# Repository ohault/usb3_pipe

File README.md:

```
                         __  _________  ____    ___  _______  ____
                        / / / / __/ _ )|_  /___/ _ \/  _/ _ \/ __/
                       / /_/ /\ \/ _  |/_ <___/ ___// // ___/ _/
                       \____/___/____/____/  /_/  /___/_/  /___/
                             Copyright (c) 2019-2026, EnjoyDigital
                                      Powered by LiteX
```

[> Intro
--------

USB3-PIPE provides **USB 3.2 SuperSpeed (Gen 1x1, 5Gbps) and SuperSpeedPlus (Gen 2x1, 10Gbps, and
Gen 1x2, 2x5Gbps, experimental) for FPGAs without any external USB chip**: the FPGA transceivers are directly connected to the USB3
connector, the PHY (USB3 PIPE + LTSSM) and a complete USB3 Device Core (Link/Protocol layers,
endpoints, device classes) are implemented in the fabric, in Migen/LiteX.

Other USB3 solutions for FPGAs rely on an external PHY ([TI TUSB1310A](http://www.ti.com/product/TUSB1310A))
or an external USB controller/FIFO ([FTDI FT60X](https://ftdichip.com/products/ft600q-b/), Infineon
[FX3](https://www.infineon.com/cms/en/product/universal-serial-bus/usb-peripheral-controllers-for-superspeed/ez-usb-fx3-usb-5-gbps-peripheral-controller/)).

**Status** (USB device, SFP2USB adapter, Linux xHCI host; Gen 1x2: experimental, two boards, see
[doc/gen1x2-hardware-validation.md](doc/gen1x2-hardware-validation.md)):

| | Gen 1x1 (5Gbps): Acorn CLE-215+ (Artix7 GTP) | Gen 2x1 (10Gbps): Alibaba XCKU3P (UltraScale+ GTY) | Gen 1x1 (5Gbps): Tang Mega 138K Pro (Gowin GW5AST GTR12) | Gen 1x2 (2x5Gbps, experimental): two Acorn Baseboard Minis + CLE-215+ (Artix7 GTP), SFP DAC cables |
|---|---|---|---|---|
| Enumeration | SuperSpeed (5000M) | SuperSpeedPlus (10000M), SuperSpeedPlus BOS capability | SuperSpeed (5000M) | SuperSpeedPlus at Gen 1x2 with a scripted USB host in gateware on the other board (enumeration-like control transfers); not yet with a USB host |
| Bulk IN/OUT | 446/449 MB/s (~90% of 5Gbps 8b/10b) | 426/466 MB/s (32-bit link), 744-785/~880 MB/s (64-bit link) | 372/433 MB/s (64-bit link at 62.5MHz) | Bulk loopback with the data checked by the scripted host (throughput not measured); PHY: 610 MB/s per direction (PRBS) |
| Full duplex | 376 + 400 MB/s | 325 + 430 MB/s (32-bit link), 619 + 736 MB/s (64-bit link) | 262 + 383 MB/s | PHY: 610 + 610 MB/s (PRBS, both directions) |
| Stability | 139 GB full duplex, data checked: 0 errors, no retry/Recovery | 156 GB full duplex (64-bit link), data checked: 0 errors, 0 LBAD, 0 Recovery | 20s runs, data checked: 0 errors, 0 LBAD, 0 Recovery | 400/400 scripted runs over 20 bitstream loads (Gen 1x2 and Gen 1x1); soak: 10000/10000 runs on one load (Gen 1x2 and Gen 1x1), 0 LBAD/retry |
| Suspend/Resume | Linux autosuspend (U3) and resume: 72/72 clean resumes (~0.6s) | | | |

Standard Linux drivers (usbfs, cdc_acm, uvcvideo, usb-storage). Demos: Bulk loopback/benchmark, LiteX
BIOS console (CDC-ACM), UVC camera up to 1080p60 (Bulk) or 1080p30 (Isochronous), Mass Storage RAM
disk (and DDR3 disk), composite camera + console.

[> Features
-----------
**PHY** (`usb3_pipe/`):
- Gen 1x1 (5Gbps): LFPS, training sequences, 8b/10b, scrambling, SKP, alignment, polarity.
- Gen 2x1 (10Gbps) on UltraScale+ GTY: SuperSpeedPlus Polling, 128b/132b, Gen 2 packet framing.
- Gen 1x2 (2x5Gbps, `lanes=2`, experimental): two lanes in lockstep, lanes deskew and swap
  (Configuration Lane detection), single lane fallback, packets at any symbol position.
- LTSSM: Polling, U0, Recovery, U1-U3, Hot/Warm Reset, Compliance, Loopback.
- Transceivers: Artix7 GTP, Kintex7 GTX, UltraScale+ GTY, Gowin GTR12, Lattice ECP5-5G DCU.
- 32, 64 or 128-bit Link Layer interface (`link_words`); the PIPE can run in its own clock
  domain (`pipe_cd`) for slower fabrics (Gowin GW5A, Lattice ECP5).
- Also generated as a standalone Verilog core (`usb3_pipe_gen`).

**USB3 Device Core** (`usb3_core/`):
- Link Layer: header flow control, retries, LMPs, timers, SuperSpeedPlus operation (Gen 2x1 and
  Gen 1x2).
- Protocol Layer, Control Endpoint (standard, class and vendor requests, Wishbone bridge).
- Bulk IN/OUT endpoints with bursts, Isochronous IN endpoints.
- U1/U2 Link Power Management (`with_lpm`), descriptors builder, debug traces.

**Device classes**: vendor Bulk, CDC-ACM (serial port, LiteX console), UVC (camera, Bulk or
Isochronous), MSC (mass storage on block RAM or DRAM), composite devices.

**Simulation**: Verilator Host model <-> PHYs <-> Device Core (`sim.py`, Gen 1x2 with `--lanes 2`),
Migen tests with Python host models (`pytest`).

*Acorn reference design (Gen 1x1 on Artix7 GTP, 32-bit Link Layer); the same PHY and core run at
Gen 2x1 on UltraScale+ GTY and on Gowin GTR12 with 64/128-bit Link Layer words.*

[> Hardware
-----------
| Board | Transceiver | Target | Status |
|---|---|---|---|
| [Acorn CLE-215+](https://github.com/enjoy-digital/litex-acorn-baseboard) on the LiteX Acorn Baseboard | Artix7 GTP | `bench/acorn.py` | Gen 1 validated, main development target |
| Alibaba Cloud XCKU3P | UltraScale+ GTY | `bench/alibaba_xcku3p.py` | Gen 1 and Gen 2 validated, main Gen 2 target |
| [Sipeed Tang Mega 138K Pro](https://wiki.sipeed.com/hardware/en/tang/tang-mega-138k/mega-138k-pro.html) | Gowin GW5AST GTR12 | `bench/sipeed_tang_mega_138k_pro.py` | Gen 1 validated |
| [LambdaConcept ECPIX-5](https://shop.lambdaconcept.com/home/46-ecpix-5.html) | Lattice ECP5-5G DCU | `bench/lambdaconcept_ecpix5.py` | Gen 1 validated: IN 434MB/s, OUT 449MB/s (on-board USB-C, open source toolchain) |
| Gowin GW5AT-15 | Gowin GTR12 | SerDes in `usb3_pipe/gw5`, no target | Gen 1 validated: IN ~400MB/s (direct USB-C) |
| [KC705](https://www.xilinx.com/products/boards-and-kits/ek-k7-kc705-g.html) | Kintex7 GTX | `bench/kc705.py` | Build-tested, hardware validation in progress |
| Two [LiteX Acorn Baseboard Minis](https://github.com/enjoy-digital/litex-acorn-baseboard) + Acorn CLE-215+, two SFP DAC cables | Artix7 GTP (both SFP cages) | `bench/acorn.py --lanes 2` | Gen 1x2 (experimental) between the two boards: PHY and Device Core with a scripted host, not yet with a USB host |

The boards without a USB connector use a [SFP2USB](http://xillybus.com/sfp2usb-module) adapter in
a SFP cage, or the [PCIsh-to-USB3.0](doc/breakout_board.pdf) breakout board
([gerbers](doc/breakout_board_gerbers.zip)). The Gowin and ECP5 targets need the GTR12 and 40-bit
`SerDesECP5` support of [LiteICLink](https://github.com/enjoy-digital/liteiclink).

Any board with a supported transceiver routed to a SFP, PCIe or USB-C connector can be used with a
target file: the example designs are shared (`usb3_core/examples.py`). Gen 2 needs 10Gbps capable
transceivers (validated on UltraScale+ GTY).

[> Getting started
------------------
Prerequisites: Python 3.9 or newer, LiteX installed with `litex_setup.py --config=standard`
([installation guide](https://github.com/enjoy-digital/litex/wiki/Installation)), Verilator for
the simulations, Vivado or the Gowin IDE for the boards.

```sh
$ git clone https://github.com/enjoy-digital/usb3_pipe && cd usb3_pipe
$ pip3 install -e .
```

Host tools and user access to the device:

```sh
$ pip3 install pyusb libusb1
$ sudo cp bench/99-usb3-pipe.rules /etc/udev/rules.d/ && sudo udevadm control --reload
```

Simulation (Verilator): Host model <-> SerDes models <-> Device PHY + USB3 Device Core.

```sh
$ ./sim.py                         # Gen 1: link training, enumeration, Bulk transfers.
$ ./sim.py --gen2 --link-words 2   # Gen 2x1 (10Gbps) with the 64-bit Link Layer.
$ ./sim.py --lanes 2 --lanes-core  # Gen 1x2 (2x5Gbps, experimental): SuperSpeedPlus on two lanes.
$ ./sim.py --help                  # Host model scenarios, pipe_cd, two lanes, VCD trace.
```

Hardware: build and load a target, check the enumeration, run a host script. The scripts given a
`--csr-csv` connect to a `litex_server` on the board bridge; `usb3_bulk.py` only needs libusb.

```sh
# Acorn CLE-215+ (Artix7 GTP, Gen 1): Bulk loopback example.
$ ./bench/acorn.py --build --load --with-jtagbone
$ lsusb -t                                           # 5000M, driver usbfs.
$ ./bench/usb3_bulk.py loopback --size 1024 --count 1000

# Alibaba XCKU3P (UltraScale+ GTY, Gen 2): bench example, 64-bit Link Layer.
$ ./bench/alibaba_xcku3p.py --build --load --example bench --gen2-capable --link-words 2
$ lsusb -t                                           # 10000M on a USB 3.2 Gen 2 root hub port, 5000M on a Gen 1 port.
$ litex_server --jtag --jtag-config <openocd config> # JTAGBone (manual: Getting started), in another terminal.
$ ./bench/usb3_bench.py both --transfer-size 65536 --csr-csv build/alibaba_xcku3p/csr.csv

# Sipeed Tang Mega 138K Pro (Gowin GW5AST GTR12, Gen 1): bench example, 64-bit Link Layer, 62.5MHz.
$ ./bench/sipeed_tang_mega_138k_pro.py --build --example bench
$ openFPGALoader -c ft2232 build/sipeed_tang_mega_138k_pro/gateware/impl/pnr/project.fs
$ litex_server --uart --uart-port /dev/ttyUSBx      # UARTBone (default bridge).
$ ./bench/usb3_bench.py both --transfer-size 65536 --csr-csv build/sipeed_tang_mega_138k_pro/csr.csv
```

`usb3_bench.py` uses 1MB transfers by default: with them the host limits the Gen 2 Bulk IN rate
(~330MB/s), `--transfer-size 65536` measures the device.

[> Demos
--------
Build with `./bench/acorn.py --build --load --example <name>`:

| Example | Device | Host side |
|---|---|---|
| `loopback` | Vendor Bulk OUT -> Bulk IN | `bench/usb3_bulk.py loopback` |
| `wishbone` | `loopback` + EP0 Wishbone bridge (vendor requests) | `litex_server --usb --usb-vid 0x1d50 --usb-pid 0x605a` |
| `bench` | Vendor Bulk counters source/checker | `bench/usb3_bench.py in\|out\|both` |
| `cdc_uartbone` | CDC-ACM serial port (UARTBone) | `litex_server --uart --uart-port /dev/ttyACM0` |
| `console` (`--cpu-type vexriscv`) | CDC-ACM LiteX BIOS console | `litex_term /dev/ttyACM0` |
| `uvc` | UVC camera, YUY2 test pattern (480p60/720p60/1080p30/1080p60) | `ffplay -f v4l2 -video_size 1920x1080 /dev/video0`, VLC |
| `uvc_iso` | UVC camera, Isochronous streaming (480p60/720p30/720p60/1080p30) | `ffplay -f v4l2 -video_size 1280x720 /dev/video0`, VLC |
| `msc` | Mass Storage 512KB FAT RAM disk | `/dev/sdX`, mount |
| `msc_dram` | Mass Storage 512MB DDR3 disk (not yet validated on hardware) | `mkfs.vfat /dev/sdX`, mount |
| `composite` (`--cpu-type vexriscv`) | UVC camera + CDC-ACM console | both at the same time |

The other targets build the same examples, except `msc_dram` (no DRAM controller). Common options:
`--link-words 1|2|4`, `--max-burst`, `--with-lpm`, `--lean`, `--with-analyzer`.

[> Standalone core generation
-----------------------------
The PHY, optionally with the Device Core (Bulk IN/OUT AXI-Stream endpoints), can be generated as a
standalone Verilog core (Gen 1x1, Artix7 GTP/Kintex7 GTX/UltraScale+ GTY) from a YAML description,
for designs not built with LiteX:
```sh
$ usb3_pipe_gen examples/a7_usb_device.yml --output-dir build/usb3_device
```
The YAML keys, interfaces and outputs are described in the Integration chapter of the manual.

[> Documentation
----------------
The **USB 3.2 PHY & Core manual** is the reference of the project, from the primers to the integration,
the examples, the debugging and the registers:

- Read it: [PDF](https://github.com/enjoy-digital/usb3_pipe/releases/download/manual-nightly/usb3_pipe_manual.pdf) or
  [HTML](https://github.com/enjoy-digital/usb3_pipe/releases/download/manual-nightly/usb3_pipe_manual.html) (rebuilt nightly).
- Sources and local build: [doc/manual](doc/manual/README.md).
- Gen 2 and multi-lane roadmap: [doc/notes/gen2-x2-roadmap.md](doc/notes/gen2-x2-roadmap.md).
- Gen 1x2 hardware validation (procedure and results between two boards):
  [doc/gen1x2-hardware-validation.md](doc/gen1x2-hardware-validation.md).

[> Tests
--------
```sh
$ pytest test                                 # Default suite: Migen tests + short Verilator simulations (marker sim).
$ pytest test -n auto -m "not slow and not sim" # Without Verilator, in parallel (pytest-xdist).
$ pytest test -m slow                         # Long Verilator simulations, run nightly by the CI.
```
The CI runs the Migen tests and the Verilator simulations on every push, the long simulations
nightly.

[> Contributing
---------------
See [CONTRIBUTING.md](CONTRIBUTING.md): tests and markers, LiteX coding style, commit/pull request
rules, hardware safety rules. Pull requests go against the default branch, one topic per pull
request.

[> License
----------
USB3-PIPE is released under the very permissive two-clause BSD license. Under the terms of this
license, you are authorized to use USB3-PIPE for closed-source proprietary designs.
Even though we do not require you to do so, those things are awesome, so please do them if possible:
 - tell us that you are using USB3-PIPE
 - cite USB3-PIPE in publications related to research it has helped
 - send us feedback and suggestions for improvements
 - send us bug reports when something goes wrong
 - send us the modifications and improvements you have done to USB3-PIPE.

[> Support and consulting
-------------------------
We love open-source hardware and like sharing our designs with others.

USB3-PIPE is developed and maintained by EnjoyDigital.

If you would like to know more about USB3-PIPE or if you are already a happy user and would like to
extend it for your needs, EnjoyDigital can provide standard commercial support as well as consulting
services.

So feel free to contact us, we'd love to work with you!

[> Contact
----------
E-mail: florent [AT] enjoy-digital.fr

[> Credits
----------
- [bunnie](https://www.bunniestudios.com/) for the [PCIsh-to-USB3.0](doc/breakout_board.pdf) breakout board
  used for the initial development.
- [Antmicro](https://antmicro.com/) and [Google](https://opensource.google/) for sponsoring the initial
  development of the project.
- The [Daisho](https://github.com/greatscottgadgets/daisho) project for its USB3 core, used initially with
  USB3-PIPE ([customized](https://github.com/enjoy-digital/daisho)) before the native USB3 Device Core.

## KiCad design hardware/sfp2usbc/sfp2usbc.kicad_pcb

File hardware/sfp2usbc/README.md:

# Dual SFP to USB-C breakout (USB 3.2 Gen 1x2)

Passive breakout for USB3-PIPE Gen 1x2 (2x5Gbps) hardware tests
([issue #140](https://github.com/enjoy-digital/usb3_pipe/issues/140),
[gen2-x2-roadmap.md](../../doc/gen2-x2-roadmap.md#gen-1x2-hardware-milestones), M1): two SFP cages
on one side, a USB Type-C receptacle on the other. The LiteX Acorn Baseboard Mini SFP-0/SFP-1
(Lane 0/Lane 1 of `bench/acorn.py --lanes 2`) are connected to the cages with two passive SFP DAC
cables, the USB-C to a USB 3.2 Gen 1x2/Gen 2x2 host with a full-featured USB-C cable.

```
 Acorn Baseboard Mini                       Breakout                                  Host
 FPGA GTP Lane 1 TX ── SFP-1 ══ DAC ══ J2 RD ── C3/C4 (AC) ──┬── J3 TX2 (B2/B3) ══ USB-C ══ RX
 FPGA GTP Lane 1 RX ── SFP-1 ══ DAC ══ J2 TD ────────────────┼── J3 RX2 (A11/A10)          TX (AC at host)
 FPGA GTP Lane 0 TX ── SFP-0 ══ DAC ══ J1 RD ── C1/C2 (AC) ──┼── J3 TX1 (A3/A2)
 FPGA GTP Lane 0 RX ── SFP-0 ══ DAC ══ J1 TD ────────────────┴── J3 RX1 (B11/B10)
                                                       U1/U2 ESD, R1/R2 Rd on CC1/CC2
```

J2 (Lane 1, Acorn SFP-1) is the top cage, J1 (Lane 0, Acorn SFP-0) the bottom cage (as the USB-C
TX2/RX2 and TX1/RX1 pins: no crossings).

## Files

| File | Role |
|---|---|
| [netlist.py](netlist.py) | Design intent: components, pins, nets (single source of truth). |
| [gen_schematic.py](gen_schematic.py) | Generates `sfp2usbc.kicad_sch` from netlist.py (KiCad library symbols, net labels, footprints). |
| [gen_board.py](gen_board.py) | Generates `sfp2usbc.kicad_pcb` (4 layers, outline, footprints/nets, placement, routing), `sfp2usbc.kicad_pro` (net classes) and `sfp2usbc.kicad_dru` (custom rules). |
| [route_board.py](route_board.py) | Routing (called by gen_board.py): planned pair routes, vias, GND planes/pours, stitching. |
| [check_netlist.py](check_netlist.py) | Checks a KiCad netlist export against netlist.py. |
| [backplane-brief.md](backplane-brief.md) | Review and fab outputs with Backplane (or in KiCad). |
| [sfp2usbc-schematic.pdf](sfp2usbc-schematic.pdf), [sfp2usbc-top.png](sfp2usbc-top.png), [sfp2usbc-bottom.png](sfp2usbc-bottom.png) | Previews (schematic, routing on F.Cu/B.Cu without the GND pours). |
| [3d/gen_models.py](3d/gen_models.py) | 3D models (VRML) of the parts missing from the KiCad 3D library: SFP cage + connector (TE 2227302), USB-C receptacle (Amphenol 12401610E4#2A, no model in KiCad 7). Referenced by the board as `${KIPRJMOD}/3d/*.wrl`. |
| [sfp2usbc-3d-sfp-side.png](sfp2usbc-3d-sfp-side.png), [sfp2usbc-3d-usb-side.png](sfp2usbc-3d-usb-side.png) | 3D views of the assembled board (KiCad 3D viewer, raytracing). |

```sh
# KiCad 7+ (kicad-cli, pcbnew Python module).
$ ./gen_schematic.py
$ kicad-cli sch export netlist --format kicadsexpr -o sfp2usbc.net sfp2usbc.kicad_sch
$ ./check_netlist.py sfp2usbc.net        # 0 errors.
$ ./gen_board.py --drc drc.rpt           # Routed board + DRC report (clean).
```

`gen_board.py` overwrites the board: once it is edited in KiCad, change the schematic (regenerated
from netlist.py) and use KiCad's "Update PCB from Schematic" (footprints linked to the schematic
symbols) instead of regenerating the board. Tests: `test/test_sfp2usbc_netlist.py` (netlist, KiCad
schematic/board round trips, DRC, pairs skew).

## Design decisions

- **AC coupling on this board, FPGA TX paths only.** The Acorn Baseboard Mini SFP lanes are DC
  coupled to the GTPs (schematic rev 0.2: "SFP: AC coupling on modules by standard") and passive DAC
  cables are DC: the USB3 transmitter AC coupling (75-265nF, 100nF as the SFP2USB adapter) is on the
  breakout, between the SFP RD pins (FPGA TX, after the DAC crossover) and the USB-C TX pins. The
  host AC couples its own TX: no capacitor on the RX paths.
- **Lane mapping.** J1 (bottom cage, to Acorn SFP-0, USB3PHY Lane 0) on TX1/RX1, J2 (top cage, to
  Acorn SFP-1, Lane 1) on TX2/RX2. With the plug in the CC1 orientation, the Configuration Lane
  (Lane 0) is TX1/RX1: lanes match. With the plug flipped, the lanes are swapped: handled in
  gateware (below).
- **Plug orientation in gateware, not with a CC controller.** Passive DAC cables do not carry the SFP
  low-speed pins (I2C, MOD_ABS...) to the other end: a CC controller on the breakout cannot be read by
  the FPGA. The host sends the SuperSpeedPlus Polling LFPS on its Configuration Lane only: the
  USB3PHY can detect the lane receiving them and swap the lanes (to do, roadmap M1). The R1/R2 pads
  give the orientation on the bench (the CC with ~0.4V-2V on its Rd is the active one).
- **UFP (device) Rd on CC1/CC2** (5.1k 1%): the host sources VBUS and enables SuperSpeed. No VCONN,
  no USB PD. VBUS is not used: the 4 VBUS pins joined, to a bottom test pad (TP1).
- **No USB 2.0** (as the SFP2USB adapter, works with Linux xHCI hosts): D+/D- and SBU1/SBU2 not
  connected.
- **P/N swaps.** USB3 receivers invert their RX polarity (host and USB3PHY, per lane, USB 3.2
  6.4.2/6.13.7), the Acorn baseboard already inverts some pairs. The routing has no crossings with
  two swaps: Lane 1 SSRX on the SFP side (J2 TD- = L1_SSRX_P: FPGA RX Lane 1 inverted) and Lane 0
  SSTX on the USB-C side (A3 TX1- = L0_SSTX_P: host RX Lane 0 inverted).
- **SFP low-speed/power pins not connected** (VccT/VccR, TX_DISABLE, MOD_DEF0-2, RS0/RS1, LOS,
  TX_FAULT): nothing to power or read in a passive DAC plug for this use.
- **ESD**: low capacitance 4-line arrays (U1/U2, TI TPD4E05U06, 0.5pF) on the USB-C side of the
  AC capacitors, close to J3. Flow-through routing: each line runs over its pad pair (1/10, 2/9,
  4/7, 5/6), the NC pads (not internally connected) are on the line's net, SSRX on the top rows,
  SSTX on the bottom rows (lines assigned in the routing order), GND vias on both sides.
- **Shield**: 1M || 100nF to GND (R3/C5, as the SFP2USB adapter). Cages to GND.

## Pin mapping

SFP host connector (SFF-8431 pinout): 1/10/11/14/17/20 VeeT/VeeR (GND), 12 RD-, 13 RD+, 18 TD+,
19 TD-, 2-9/15/16 low-speed/power (not connected). Through the DAC cable, the Acorn TD (FPGA TX)
arrives on the breakout RD pins and the breakout TD pins go to the Acorn RD (FPGA RX).

| Net | SFP | AC cap | USB-C | ESD |
|---|---|---|---|---|
| L0_SFP_RD_P / L0_SSTX_P | J1.13 (RD+) | C1 | A3 (TX1-, swapped) | U1.4/7 |
| L0_SFP_RD_N / L0_SSTX_N | J1.12 (RD-) | C2 | A2 (TX1+, swapped) | U1.5/6 |
| L0_SSRX_P | J1.18 (TD+) | - | B11 (RX1+) | U1.2/9 |
| L0_SSRX_N | J1.19 (TD-) | - | B10 (RX1-) | U1.1/10 |
| L1_SFP_RD_P / L1_SSTX_P | J2.13 (RD+) | C3 | B2 (TX2+) | U2.4/7 |
| L1_SFP_RD_N / L1_SSTX_N | J2.12 (RD-) | C4 | B3 (TX2-) | U2.5/6 |
| L1_SSRX_P | J2.19 (TD-, swapped) | - | A11 (RX2+) | U2.1/10 |
| L1_SSRX_N | J2.18 (TD+, swapped) | - | A10 (RX2-) | U2.2/9 |
| CC1 / CC2 | | | A5 / B5 | R1 / R2 5.1k to GND |
| VBUS | | | A4/A9/B4/B9 | TP1 (bottom) |
| SHIELD | | | Shell | R3 1M, C5 100nF to GND |
| GND | 1/10/11/14/17/20, cages | | A1/A12/B1/B12 | U1/U2.3/8 |

## Bill of materials

| Ref | Part | KiCad footprint | Notes |
|---|---|---|---|
| J1, J2 | SFP 20-pin connector + 1x1 press-fit cage (TE drawing 2227302) | `Connector:Connector_SFP_and_Cage` | Order the connector and the cage per the TE drawing; PCB edge 43mm from the footprint origin. |
| J3 | Amphenol 12401610E4#2A (USB-C, 24 pins, USB 3.2, R/A SMT) | `Connector_USB:USB_C_Receptacle_Amphenol_12401610E4-2A` | All 4 SuperSpeed pairs (the 16-pin USB 2.0 receptacles, ex GCT USB4085, do not fit). Alternative: Molex 105450-0101. |
| C1-C4 | 100nF X7R 0402, 16V | `Capacitor_SMD:C_0402_1005Metric` | USB3 75-265nF. |
| U1, U2 | TI TPD4E05U06DQAR | `Package_SON:USON-10_2.5x1.0mm_P0.5mm` | 0.5pF, flow-through. |
| R1, R2 | 5.1k 1% 0402 | `Resistor_SMD:R_0402_1005Metric` | Rd (UFP). |
| R3, C5 | 1M 0402, 100nF 0402 | 0402 | Shield. |
| TP1 | VBUS test pad (bottom side) | `TestPoint:TestPoint_Pad_D1.0mm` | |
| H1-H4 | M3 mounting holes | `MountingHole:MountingHole_3.2mm_M3` | |

Check the datasheets, availability and footprints (pad sizes, J3 front/board edge position) before
ordering.

## PCB

Generated (gen_board.py + route_board.py), DRC clean (KiCad 7: 0 violations, 0 unconnected).

- **Stackup**: 4 layers, 1.6mm: F.Cu signals, In1.Cu/In2.Cu solid GND planes, B.Cu signals (USB-C B
  row pairs, CC2, VBUS, shield ring), GND pours on F.Cu/B.Cu, GND stitching vias (3mm grid where
  free). Set the fab's controlled impedance stackup.
- **Impedance**: 90 ohm differential (USB 3.2; SFP is 100 ohm: negligible on a few cm), net class
  `HS_90R` (all `L*` nets) with 0.30mm width/0.20mm gap: estimate for a ~0.21mm prepreg, to replace
  with the fab's stackup/impedance calculator values (then regenerate: PAIR_PITCH/HS_WIDTH in
  route_board.py). Custom rule: 0.25mm between the HS tracks and the other nets outside the fine
  pitch footprints.
- **Placement**: 78 x 50mm, cages on the left edge (TE 2227302 PCB edge), J3 on the right edge, AC
  caps in line with the SFP RD pads (staggered), ESD arrays (flow-through) between the caps and J3,
  Rd/shield parts next to J3, 4 M3 holes on the right half (the cages take the left half).
- **Routing** (per lane, nested L-shaped routes with 45 degrees corners, no crossings):
  - USB-C A row pairs (L1 SSRX, L0 SSTX) on F.Cu end to end, no vias.
  - USB-C B row pairs (L1 SSTX, L0 SSRX): F.Cu from the SFP to the ESD, then 0.35/0.2mm vias
    (staggered 0.6mm, GND stitching via next to them), B.Cu, and 0.35/0.2mm vias in front of the B
    row (two staggered columns under the connector body: tented), F.Cu stubs to the B pads. A row
    GND/VBUS pins joined to their B row pins across the rows.
  - Lengths 34-36mm per line (lanes within ~2mm, deskewed by the USB3PHY), intra-pair skew <=
    0.043mm: the B row pairs P line (outer via column) is matched with 3 bumps on the N line.
- **Fab**: 0.35mm vias with 0.2mm drills (0.075mm annular ring), 0.15mm clearances, 0.25mm hole
  clearance, 0.25mm copper to edge (J3 footprint: 0.298mm between a NPTH and a shell pad): check
  them against the fab capabilities.
- **To review in KiCad**: impedance values, return paths (GND planes are solid under all the pairs),
  the J3/SFP footprints vs datasheets, the vias under the J3 body (tented), silkscreen.
- **Outputs**: Gerbers, drill, IPC netlist, BOM, placement (CPL), fab stackup/impedance notes.
- **3D**: KiCad 3D viewer (View > 3D Viewer, Preferences > Raytracing) with the KiCad 3D library
  (0402, USON-10) and the `3d/` models (approximate shapes: use the manufacturers' STEP files for
  enclosure work). The previews are KiCad 7 3D viewer raytraced views; KiCad 8+:
  `kicad-cli pcb render --quality high` for the same renders from the command line.

## Bring-up

1. Continuity/impedance: no short between pairs, Rd 5.1k on CC1/CC2, AC caps in series on the TX paths.
   DAC cables: Acorn SFP-0 to J1 (bottom cage), SFP-1 to J2 (top cage).
2. Acorn `bench/acorn.py --lanes 2 --role device` on both SFPs through the breakout and DAC cables
   (<= 1m, passive), a full-featured USB-C cable (all SuperSpeed pairs: "USB 10Gbps/20Gbps" rated)
   to a USB 3.2 Gen 2x2 host (Gen 1x2 support: ex ASMedia ASM3242).
3. `./bench/usb3_lanes.py status`: SuperSpeedPlus Polling with Gen 1x2 negotiated (x2) and link
   training, both plug orientations (flipped: lanes swapped, until the gateware lane swap is done).
   The `--lanes 2` bitstream has no Link Layer: the host does not enumerate it (the link leaves U0).
   Linux `/sys/bus/usb/devices/*/rx_lanes`/`tx_lanes` once the Gen 1x2 Link Layer is done.
4. Single lane (Gen 1x1) hosts: needs the single lane fallback in the USB3PHY (roadmap).

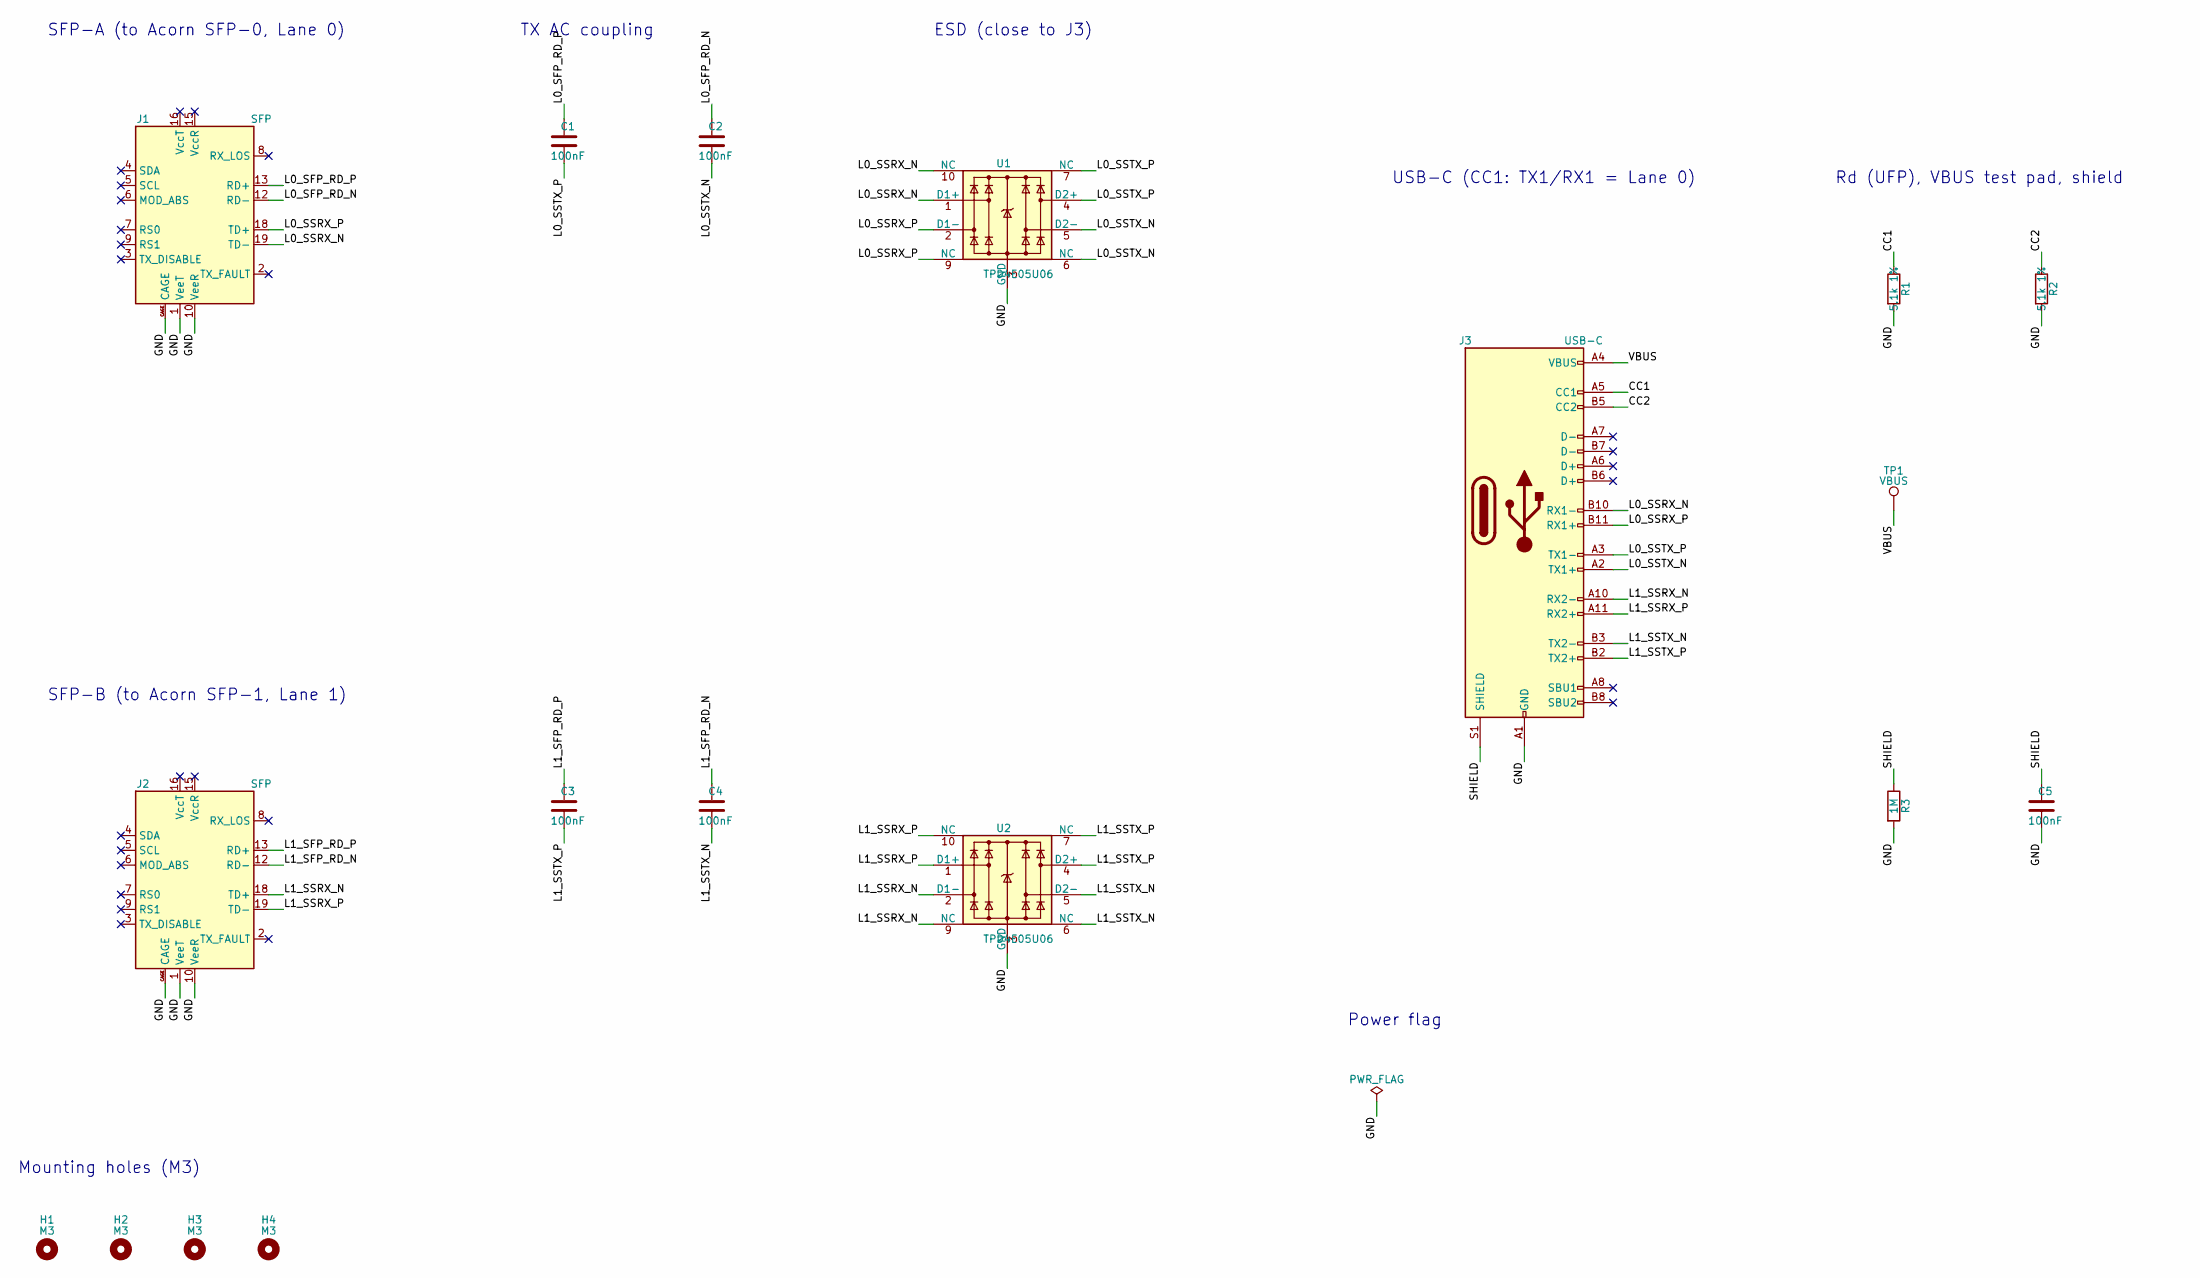
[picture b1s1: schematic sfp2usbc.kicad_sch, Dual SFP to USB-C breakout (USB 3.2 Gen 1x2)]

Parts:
C1, C2, C3, C4, C5: 100nF; C_0402_1005Metric
H1, H2, H3, H4: M3; MountingHole_3.2mm_M3
J1, J2: SFP; Connector_SFP_and_Cage
J3: USB-C; USB_C_Receptacle_Amphenol_12401610E4-2A
R1, R2: 5.1k 1%; R_0402_1005Metric
R3: 1M; R_0402_1005Metric
TP1: VBUS; TestPoint_Pad_D1.0mm
U1, U2: TPD4E05U06; USON-10_2.5x1.0mm_P0.5mm

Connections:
/CC1: J3.A5 (CC1), R1.1
/CC2: J3.B5 (CC2), R2.1
/GND: C5.2, J1.1 (VeeT), J1.10 (VeeR), J1.11 (VeeR), J1.14 (VeeR), J1.17 (VeeT), J1.20 (VeeT), J1.CAGE, J2.1 (VeeT), J2.10 (VeeR), J2.11 (VeeR), J2.14 (VeeR), J2.17 (VeeT), J2.20 (VeeT), J2.CAGE, J3.A1 (GND), J3.A12 (GND), J3.B1 (GND), J3.B12 (GND), R1.2, R2.2, R3.2, U1.3 (GND), U1.8 (GND), U2.3 (GND), U2.8 (GND)
/L0_SFP_RD_N: C2.1, J1.12 (RD-)
/L0_SFP_RD_P: C1.1, J1.13 (RD+)
/L0_SSRX_N: J1.19 (TD-), J3.B10 (RX1-), U1.1 (D1+), U1.10 (NC)
/L0_SSRX_P: J1.18 (TD+), J3.B11 (RX1+), U1.2 (D1-), U1.9 (NC)
/L0_SSTX_N: C2.2, J3.A2 (TX1+), U1.5 (D2-), U1.6 (NC)
/L0_SSTX_P: C1.2, J3.A3 (TX1-), U1.4 (D2+), U1.7 (NC)
/L1_SFP_RD_N: C4.1, J2.12 (RD-)
/L1_SFP_RD_P: C3.1, J2.13 (RD+)
/L1_SSRX_N: J2.18 (TD+), J3.A10 (RX2-), U2.2 (D1-), U2.9 (NC)
/L1_SSRX_P: J2.19 (TD-), J3.A11 (RX2+), U2.1 (D1+), U2.10 (NC)
/L1_SSTX_N: C4.2, J3.B3 (TX2-), U2.5 (D2-), U2.6 (NC)
/L1_SSTX_P: C3.2, J3.B2 (TX2+), U2.4 (D2+), U2.7 (NC)
/SHIELD: C5.1, J3.S1 (SHIELD), R3.1
/VBUS: J3.A4 (VBUS), J3.A9 (VBUS), J3.B4 (VBUS), J3.B9 (VBUS), TP1.1

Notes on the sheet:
SFP-A (to Acorn SFP-0, Lane 0)
SFP-B (to Acorn SFP-1, Lane 1)
TX AC coupling
ESD (close to J3)
USB-C (CC1: TX1/RX1 = Lane 0)
Rd (UFP), VBUS test pad, shield
Power flag
Mounting holes (M3)

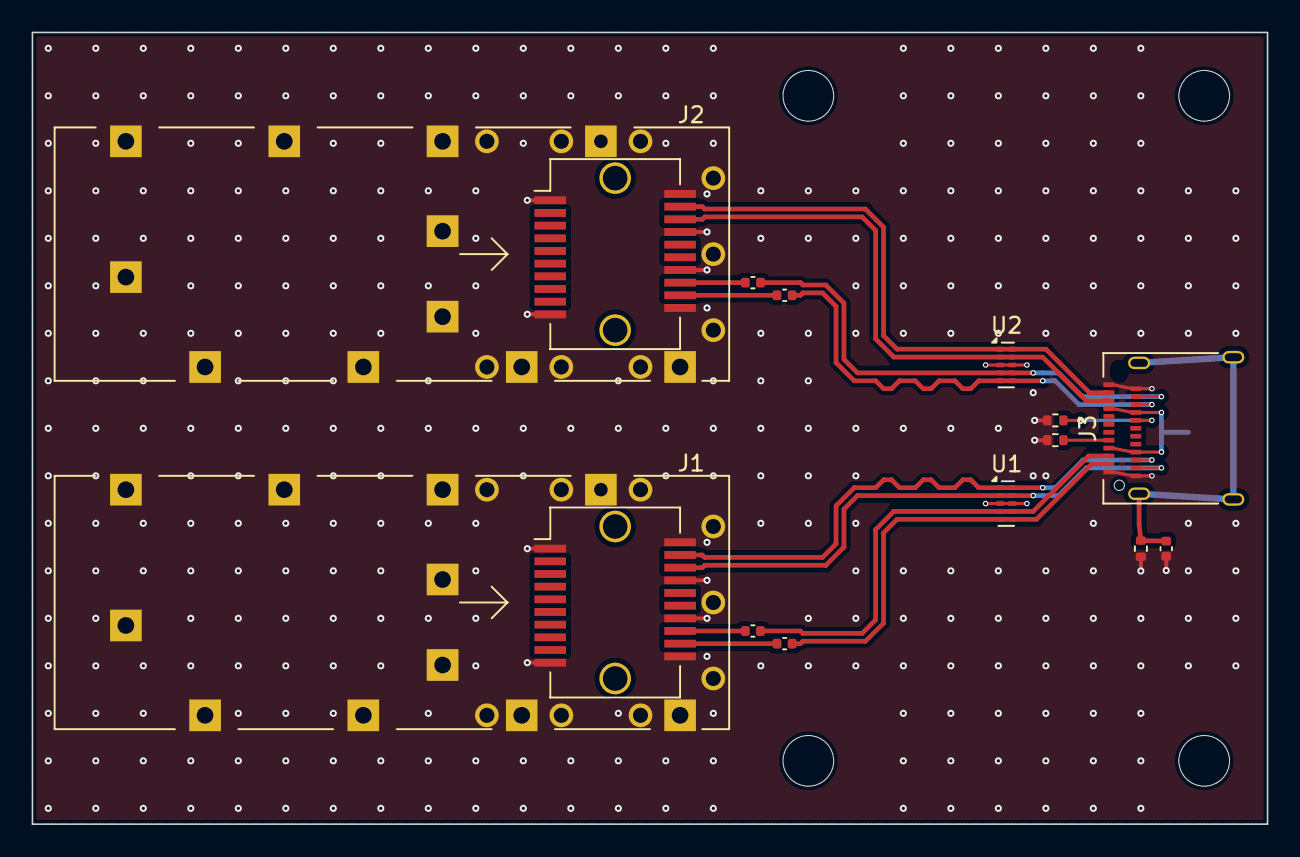
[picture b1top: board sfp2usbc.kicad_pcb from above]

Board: 4 copper layers, 78.0 x 50.0 mm, 18 parts (1 on the bottom side), 17 nets.

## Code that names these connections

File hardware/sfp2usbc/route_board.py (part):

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    # Lane 1 SSTX (B2/B3): ESD bottom rows -> vias (staggered) -> B.Cu -> B row vias.
    (_, y_tx_p) = r.check("U2", "7", "L1_SSTX_P")
    xv = {"L1_SSTX_P": 163.2, "L1_SSTX_N": 163.8}
    for pin, net in [("7", "L1_SSTX_P"), ("6", "L1_SSTX_N")]:
        (px, py) = r.check("U2", pin, net)
        r.track(net, F, [(px, py), (xv[net], py)], HS_WIDTH)
        r.via(net, (xv[net], py), HS_VIA)
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    # Lane 0 SSRX (B10/B11): ESD top rows -> vias (staggered) -> B.Cu -> B row vias.
    (_, y_rx_n) = r.check("U1", "10", "L0_SSRX_N")
    xv = {"L0_SSRX_N": 163.8, "L0_SSRX_P": 163.2}
    for pin, net in [("10", "L0_SSRX_N"), ("9", "L0_SSRX_P")]:
        (px, py) = r.check("U1", pin, net)
        r.track(net, F, [(px, py), (xv[net], py)], HS_WIDTH)
        r.via(net, (xv[net], py), HS_VIA)
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

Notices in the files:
hardware/sfp2usbc/route_board.py:
Copyright (c) 2026 Florent Kermarrec <florent@enjoy-digital.fr>
SPDX-License-Identifier: BSD-2-Clause
README.md:
License: BSD 2-Clause
